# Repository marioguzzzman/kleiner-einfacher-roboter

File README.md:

# Mini Robot Swarm Unit — "Little Dog"

A small 3D-printed quadruped robot, built as one unit of a larger robotic swarm.
Each unit senses its surroundings, moves on four servo legs, and (from v2 onward)
has a synthesized "voice." This repository holds **two hardware/firmware
generations** of the same physical robot plus the **shared** mechanical body and
carrier PCB.

> The 3D body and the carrier PCB are common to both generations — only the
> microcontroller board and the firmware changed between v1 and v2.

---

## Two generations

| | **v1** | **v2** |
|---|--------|--------|
| Folder | [`v1/`](v1/) | [`v2/`](v2/) |
| MCU | Adafruit Feather ESP32 V2 | ESP32-C3 SuperMini |
| Servos | 4× MG90S | 4× MS18 (SG90-class) |
| Sensing | HC-SR04 ultrasonic | HC-SR04 ultrasonic (+ 1k/2k echo divider) |
| Audio | — | MAX98357A I2S amp + speaker ("modem voice") |
| Behavior | pose-based (sit / wave / walk / lay down) | trot + obstacle-stop (<10 cm) + voice on stop |
| I2C pins | GPIO21/22 | GPIO6/7 |
| Status | Phase 1 baseline | **electronics bring-up complete** |

**v2 is a continuation of v1**, not a separate project — same robot, new brain.

---

## Repository layout

```
kleiner-einfacher-roboter/
├── README.md                       ← you are here
├── LICENSE
├── robot_dog_pcb/                   KiCad carrier PCB          (SHARED)
├── little_robot_original_3d_stl/    printable body/legs/cover  (SHARED)
├── v1/   Feather ESP32 V2, pose-based
│   ├── README.md
│   ├── docs/          hardware.md · setup.md · code_explanation.md
│   └── src/           robot_dog.ino
└── v2/   ESP32-C3 SuperMini, walk + sensor + voice
    ├── README.md
    ├── firmware/
    │   ├── little_dog_walk/     ⭐ main program (walk + stop + voice)
    │   ├── little_dog_test_1/   full 5-part functionality test
    │   ├── little_dog_test_v2/  flag-based staged test
    │   ├── obstacle_stop/       walk + stop demo (simple chirp)
    │   └── diagnostics/         per-subsystem isolation sketches
    └── docs/          HANDOFF_WIRING.md · HANDOFF_LEARNINGS.md
```

---

## Shared hardware

- **Body:** `little_robot_original_3d_stl/` — `main_body.stl`, `leg.stl`, `cover.stl`.
  Based on the [Cobot Four-Servo-Legs Robot](https://makerworld.com/en/models/523448-cobot-four-servo-legs-and-distance-sensor-robot) on MakerWorld.
- **Carrier PCB:** `robot_dog_pcb/` — KiCad project (schematic, board, `.pdf` export).
  Modules mount as pluggable headers on the carrier.

---

## Getting started

- Building the **current** robot → see **[v2/README.md](v2/)** and
  [v2/docs/HANDOFF_WIRING.md](v2/docs/HANDOFF_WIRING.md) for the full wiring schematic.
- The **original** design → see **[v1/README.md](v1/)**.

---

## License

See [LICENSE](LICENSE). (Original note: all rights reserved.)

## Credits

- 3D model: [Cobot Four Servo Legs Robot](https://makerworld.com/en/models/523448-cobot-four-servo-legs-and-distance-sensor-robot) on MakerWorld
- Built with Arduino / ESP32, PCA9685, MAX98357A, and Adafruit libraries.

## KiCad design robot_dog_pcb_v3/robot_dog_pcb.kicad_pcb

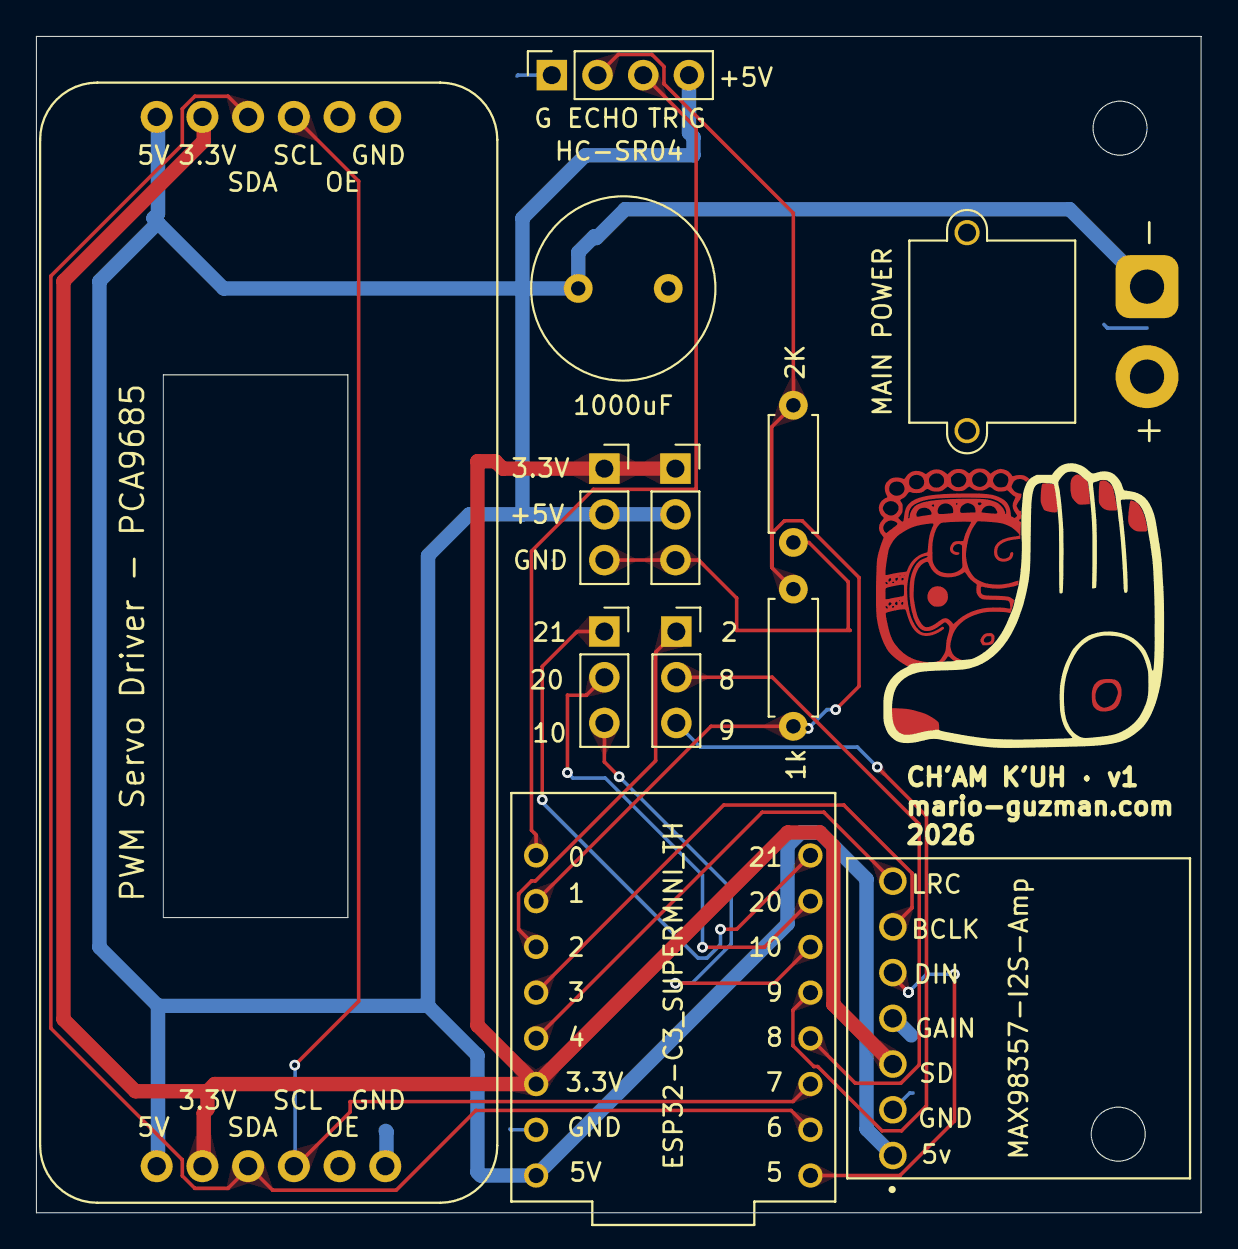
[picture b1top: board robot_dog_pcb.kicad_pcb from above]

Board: 2 copper layers, 64.7 x 65.3 mm, 14 parts (0 on the bottom side), 16 nets.

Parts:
C1: 1000uF; C_Radial_D10.0mm_H12.5mm_P5.00mm
H1, H3: MountingHole; MountingHole_3mm
J1: MAIN POWER; AMASS_XT30PW-M_1x02_P2.50mm_Horizontal
J2, J4: GPIO; PinSocket_1x03_P2.54mm_Vertical
J3: HC-SR04; PinSocket_1x04_P2.54mm_Vertical
J5, J6: Extra power; PinSocket_1x03_P2.54mm_Vertical
R2: 2K; R_Axial_DIN0207_L6.3mm_D2.5mm_P7.62mm_Horizontal
R3: 1k; R_Axial_DIN0207_L6.3mm_D2.5mm_P7.62mm_Horizontal
U1: ESP32-C3_SUPERMINI_TH; MODULE_ESP32-C3_SUPERMINI_TH
U2: MAX98357-I2S-Amp; Adafruit-MAX98357-I2S-Amp-Breakout
U3: Adafruit-16-Channel-PWM-Servo-Driver-PCB; PCB ONLY Adafruit-16-Channel-PWM-Servo-Driver-PCB

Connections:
/BCLK: U1.3 (GPIO3), U2.JP1_6 (BCLK)
/DIN: U1.5 (GPIO5), U2.JP1_5 (DIN)
/ECHO: J3.2, R2.2, R3.1, R3.2, U1.1 (GPIO1)
/GPI02: J4.1, U1.2 (GPIO2)
/GPI08: J4.2, U1.8 (GPIO8)
/GPI09: J4.3, U1.9 (GPIO9)
/GPI10: J2.3, U1.10 (GPIO10)
/GPI020: J2.2, U1.20 (GPIO20)
/GPI021: J2.1, U1.21 (GPIO21)
/LRCLK: U1.4 (GPIO4), U2.JP1_7 (LRCLK)
/SCL: U1.7 (GPIO7), U3.SCL_1 (SCL), U3.SCL_2 (SCL)
/SDA: U1.6 (GPIO6), U3.SDA_1 (SDA), U3.SDA_2 (SDA)
/TRIG: J3.3, U1.0 (GPIO0)
GND: C1.2, J1.2 (GND_MAIN), J3.1 (GND), J5.3, J6.3, R2.1, U1.G (GND), U2.JP1_2 (GND), U2.JP1_4 (GAIN), U3.GND_1 (GND), U3.GND_2 (GND)
V+: C1.1, J1.1 (5V_MAIN), J3.4, J5.2, J6.2, U1.5V, U2.JP1_1 (VDD), U3.V+_1 (V+), U3.V+_2 (V+)
VCC: J5.1, J6.1, U1.3.3 (3V3), U2.JP1_3 (SD), U3.VCC_1 (VCC), U3.VCC_2 (VCC)

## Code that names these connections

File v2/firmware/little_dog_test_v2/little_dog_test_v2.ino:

/*
 * "Little Dog" Quadruped — Staged Functionality Test (v2)
 * =======================================================
 * Isolates each subsystem so you never debug "all problems at once."
 *
 * >>> FIRST, IN THE ARDUINO IDE: Tools -> "USB CDC On Boot" -> ENABLED <<<
 *     Without it the ESP32-C3 prints nothing over USB and looks frozen.
 *
 * Turn subsystems on/off with the flags below. Start with ONLY legs:
 *   TEST_LEGS 1, TEST_DISTANCE 0, TEST_AUDIO 0
 * Once legs work, turn on distance, then audio.
 *
 * LEG MAP (confirm by watching Stage 1):
 *   ch0 = back-left   ch1 = back-right   ch2 = front-left   ch3 = front-right
 *
 * PINS (ESP32-C3 SuperMini):
 *   GPIO0 TRIG  GPIO1 ECHO(div)  GPIO3 BCLK  GPIO4 LRC  GPIO5 DIN
 *   GPIO6 SDA   GPIO7 SCL        GPIO10 OE
 */

// ===================== FEATURE FLAGS =====================
#define TEST_LEGS      1     // set 0 to skip
#define TEST_DISTANCE  1     // set 0 to skip
#define TEST_AUDIO     1     // set 0 to skip (and skips I2S init entirely)
// =========================================================

#include <Wire.h>
#include <Adafruit_PWMServoDriver.h>
#if TEST_AUDIO
  #include "driver/i2s.h"
#endif

// ---------- pins ----------
#define PIN_TRIG 0
#define PIN_ECHO 1
#define PIN_SDA  6
#define PIN_SCL  7
#define PIN_OE   10
#define I2S_BCLK 3
#define I2S_LRC  4
#define I2S_DIN  5

// ---------- servo driver ----------
Adafruit_PWMServoDriver pwm = Adafruit_PWMServoDriver(0x40);
#define SERVO_FREQ 50
#define CENTER 307          // ~1.5 ms
#define SWING   60          // gentle; raise once safe range known

const char* LEG_NAME[4] = {"ch0 BACK-LEFT", "ch1 BACK-RIGHT",
                           "ch2 FRONT-LEFT", "ch3 FRONT-RIGHT"};

// ---------- audio ----------
#if TEST_AUDIO
  #define SAMPLE_RATE 16000
  #define I2S_PORT I2S_NUM_0
#endif

unsigned long loopCount = 0;

// =====================================================
void setup() {
  Serial.begin(115200);
  delay(1500);
  Serial.println("\n\n=== Little Dog Test v2 — staged ===");
  Serial.printf("Flags: LEGS=%d DISTANCE=%d AUDIO=%d\n",
                TEST_LEGS, TEST_DISTANCE, TEST_AUDIO);

  // OE: hold servos disabled during init (harmless if OE not wired)
  pinMode(PIN_OE, OUTPUT);
  digitalWrite(PIN_OE, HIGH);

  Serial.println("[init] I2C...");
  Wire.begin(PIN_SDA, PIN_SCL);
  scanI2C();

  Serial.println("[init] PCA9685...");
  pwm.begin();
  pwm.setPWMFreq(SERVO_FREQ);

#if TEST_DISTANCE
  pinMode(PIN_TRIG, OUTPUT);
  pinMode(PIN_ECHO, INPUT);
  digitalWrite(PIN_TRIG, LOW);
#endif

#if TEST_AUDIO
  Serial.println("[init] I2S...");
  setupI2S();
#endif

  digitalWrite(PIN_OE, LOW);   // enable servo outputs
  centerAll();
  Serial.println("[init] done. Legs centered.\n");
  delay(1500);
}

// =====================================================
void loop() {
  Serial.printf("---- heartbeat %lu ----\n", loopCount++);

#if TEST_LEGS
  Serial.println("[STAGE 1] legs — one at a time");
  centerAll();
  delay(600);
  for (int ch = 0; ch < 4; ch++) {
    Serial.printf("   moving %s\n", LEG_NAME[ch]);
    pwm.setPWM(ch, 0, CENTER + SWING); delay(500);
    pwm.setPWM(ch, 0, CENTER - SWING); delay(500);
    pwm.setPWM(ch, 0, CENTER);         delay(400);
  }
  Serial.println("[STAGE 1] done\n");
  delay(600);
#endif

#if TEST_DISTANCE
  Serial.println("[STAGE 2] distance");
  for (int i = 0; i < 3; i++) {
    long d = readDistanceCM();
    if (d < 0) Serial.println("   (no echo — check divider/wiring)");
    else       Serial.printf("   %ld cm\n", d);
    delay(300);
  }
  Serial.println("[STAGE 2] done\n");
#endif

#if TEST_AUDIO
  Serial.println("[STAGE 3] chirp");
  playTone(700, 120);
  delay(80);
  playTone(1000, 120);
  Serial.println("[STAGE 3] done\n");
#endif

  delay(1500);
}

// =====================================================
void centerAll() {
  for (int ch = 0; ch < 4; ch++) pwm.setPWM(ch, 0, CENTER);
}

void scanI2C() {
  bool found = false;
  for (byte a = 1; a < 127; a++) {
    Wire.beginTransmission(a);
    if (Wire.endTransmission() == 0) {
      Serial.printf("   I2C found 0x%02X\n", a);
      found = true;
    }
  }
  if (!found)
    Serial.println("   I2C: NONE found — servos won't move. Check SDA/SCL/power.");
}

#if TEST_DISTANCE
long readDistanceCM() {
  digitalWrite(PIN_TRIG, LOW);  delayMicroseconds(2);
  digitalWrite(PIN_TRIG, HIGH); delayMicroseconds(10);
  digitalWrite(PIN_TRIG, LOW);
  long dur = pulseIn(PIN_ECHO, HIGH, 30000UL);  // 30 ms timeout
  if (dur == 0) return -1;
  return dur / 58;
}
#endif

#if TEST_AUDIO
void setupI2S() {
  i2s_config_t cfg = {
    .mode = (i2s_mode_t)(I2S_MODE_MASTER | I2S_MODE_TX),
    .sample_rate = SAMPLE_RATE,
    .bits_per_sample = I2S_BITS_PER_SAMPLE_16BIT,
    .channel_format = I2S_CHANNEL_FMT_ONLY_LEFT,
    .communication_format = I2S_COMM_FORMAT_STAND_I2S,
    .intr_alloc_flags = 0,
    .dma_buf_count = 8,
    .dma_buf_len = 64,
    .use_apll = false,
    .tx_desc_auto_clear = true,
    .fixed_mclk = 0
  };
  i2s_pin_config_t pins = {
    .bck_io_num = I2S_BCLK,
    .ws_io_num = I2S_LRC,
    .data_out_num = I2S_DIN,
    .data_in_num = I2S_PIN_NO_CHANGE
  };
  if (i2s_driver_install(I2S_PORT, &cfg, 0, NULL) != ESP_OK) {
    Serial.println("   I2S install FAILED");
    return;
  }
  i2s_set_pin(I2S_PORT, &pins);
  i2s_zero_dma_buffer(I2S_PORT);
}

// Non-blocking-ish: each write has a timeout so audio can NEVER
// freeze the whole sketch (the old portMAX_DELAY could hang forever).
void playTone(float freq, int ms) {
  const int amp = 8000;
  int n = (SAMPLE_RATE * ms) / 1000;
  size_t bw;
  static float ph = 0.0f;
  float inc = 2.0f * 3.14159265f * freq / SAMPLE_RATE;
  for (int i = 0; i < n; i++) {
    int16_t s = (int16_t)(amp * sinf(ph));
    ph += inc; if (ph > 6.2831853f) ph -= 6.2831853f;
    esp_err_t r = i2s_write(I2S_PORT, &s, sizeof(s), &bw, pdMS_TO_TICKS(20));
    if (r != ESP_OK || bw == 0) break;  // don't hang if I2S stalls
  }
  i2s_zero_dma_buffer(I2S_PORT);
}
#endif

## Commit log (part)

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2026-06-12 Initial upload
